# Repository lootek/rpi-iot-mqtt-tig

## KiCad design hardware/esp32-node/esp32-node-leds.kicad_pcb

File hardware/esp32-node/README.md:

# esp32 node v1 - carrier for the 30-pin ESP32 DevKit V1

86 x 54 mm, 2-layer FR-4, DRC clean (KiCad 10: 0 violations, 0 unconnected). Used by the shed, office and dining_room nodes
(see ~/ai/esp32-weather-v2 spec). Populate only what a node needs; the shed needs just the BME280 socket.
Files: `esp32-node.kicad_pcb` + `esp32-node-gerbers.zip` (v1: LEDs external on a 4-way terminal), `esp32-node-leds.kicad_pcb` + `esp32-node-leds-gerbers.zip` (v1b: 3 LEDs soldered on the board), `gen_esp32.py` (regenerates both; `--leds-onboard` for v1b), `esp32-wiring.svg/png` (wiring diagram, `gen-esp32-wiring.py`).
Order one of the two Gerber zips. v1b has 5 mm LEDs (green, yellow, red) at the left edge, 7 mm apart, long leg (anode) toward the resistors.

## DevKit and orientation
30-pin DOIT-style DevKit V1 (USB-C, CH340), two 1x15 headers **25.4 mm apart** (10 pitches).
Plan view: USB end of the DevKit at the bottom edge of the PCB (it overhangs a little).
Left header top to bottom: EN VP VN D34 D35 D32 D33 D25 D26 D27 D14 D12 D13 GND VIN.
Right header top to bottom: D23 D22 TX0 RX0 D21 D19 D18 D5 D17 D16 D4 D2 D15 GND 3V3.

## Nets
| ESP32 pin | Signal | Goes to |
|---|---|---|
| 3V3 | 3V3 | BME280 VCC + CSB, SCD30 VIN, DHT22 +, C1 |
| GND | GND | ground pour on both layers, BME280 GND + SDO, SCD30 GND, DHT22 -, LED cathodes |
| D21 | SDA | BME280 SDA, SCD30 SDA |
| D22 | SCL | BME280 SCL, SCD30 SCL |
| D4 | DHT data | DHT22 DAT |
| D25 / D26 / D27 | LED green / yellow / red | 220 ohm each, then the LED terminal |

BME280 address pins are tied on the board (CSB to 3V3 = I2C mode, SDO to GND = address 0x76).
The DHT22 terminal expects a 3-pin module with its own pull-up; a bare 4-pin DHT22 needs a 10k from DAT to 3V3 added by hand.

## Connectors (5.08 mm screw terminals, wire entry faces the board edge)
- LED terminal, left edge, top to bottom: **G Y R K**. Each LED anode to its terminal, all cathodes to K. 220 ohm resistors R3-R5 are on the board.
- SCD30 terminal, right edge, top to bottom: **3V3 GND SCL SDA**.
- DHT22 terminal, right edge, top to bottom: **3V3 DAT GND**.
- BME280: 1x6 female socket, pins VCC GND SCL SDA CSB SDO (GY-BME280 order). Plug the module so it lies to the **right** of the socket (away from the DevKit).

## BOM
| Ref | Part |
|---|---|
| J1, J2 | 1x15 female header 2.54 mm, 2 pcs (DevKit sockets) |
| J3 | 4-pole screw terminal 5.08 mm (LEDs) |
| J4 | 1x6 female header 2.54 mm (BME280) |
| J5 | 4-pole screw terminal 5.08 mm (SCD30) |
| J6 | 3-pole screw terminal 5.08 mm (DHT22) |
| R3-R5 | 220 ohm 1/4 W axial |
| C1 | 100 nF ceramic disc, 2.5 mm lead spacing |

## Order settings
2 layers, 86 x 54 mm, qty 5+, FR-4 1.6 mm, HASL, no assembly. Upload `esp32-node-gerbers.zip` as is.

## Check before ordering
- Row spacing 25.4 mm was derived from the DevKit photos (11 holes counted inclusively on the perfboard = 10 pitches); measure your DevKit's pin rows once with a ruler.
- Terminal wire-entry side was confirmed from the KiCad 3D model, not a datasheet.
- Not test-fitted on real hardware. The BME280 module must not extend left over the DevKit.

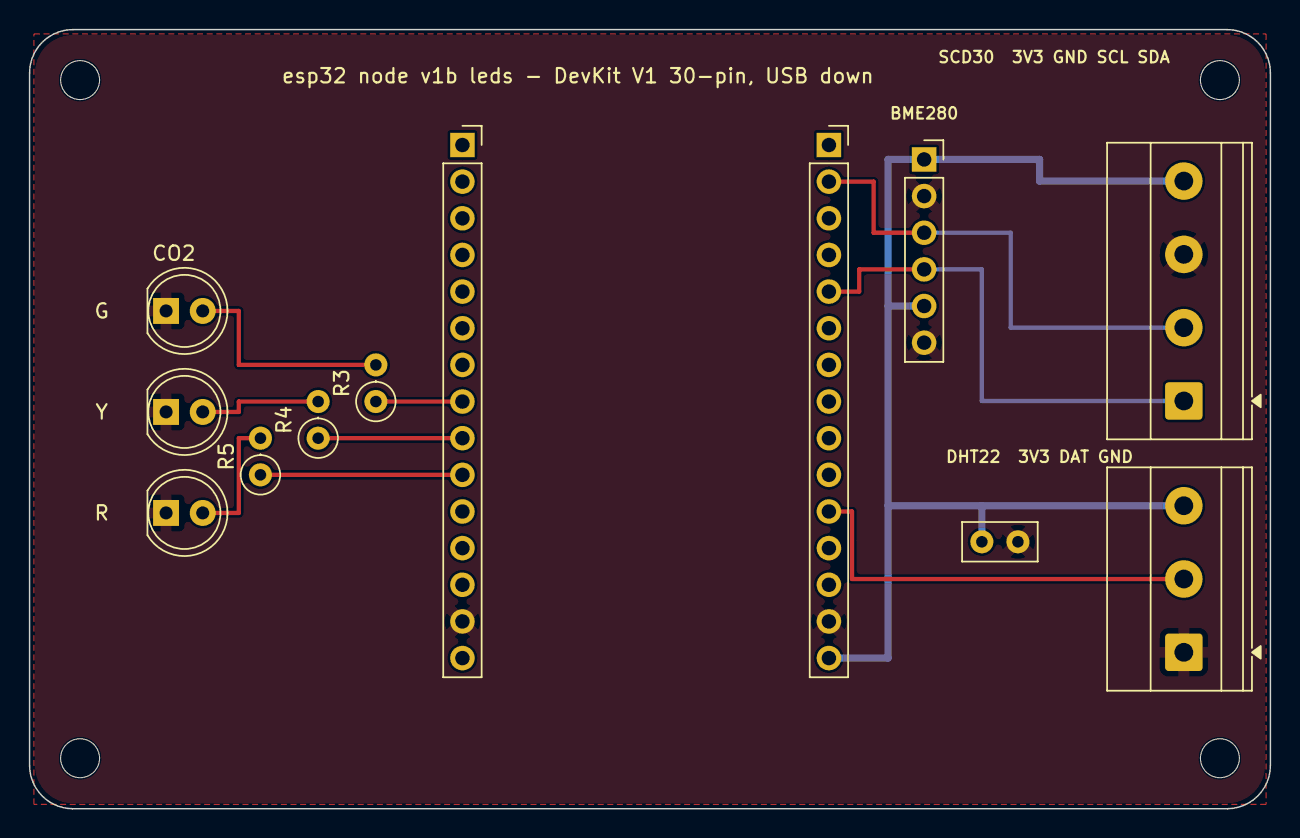
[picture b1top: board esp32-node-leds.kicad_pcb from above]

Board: 2 copper layers, 86.0 x 54.0 mm, 16 parts (0 on the bottom side), 11 nets.

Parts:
C1: 100n; C_Disc_D5.0mm_W2.5mm_P2.50mm
D1, D2, D3: LED; LED_D5.0mm
H1, H2, H3, H4: M2.5; MountingHole_2.7mm_M2.5
J1: ESP32 left; PinSocket_1x15_P2.54mm_Vertical
J2: ESP32 right; PinSocket_1x15_P2.54mm_Vertical
J4: BME280; PinSocket_1x06_P2.54mm_Vertical
J5: SCD30; TerminalBlock_Phoenix_MKDS-1,5-4-5.08_1x04_P5.08mm_Horizont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
J6: DHT22; TerminalBlock_Phoenix_MKDS-1,5-3-5.08_1x03_P5.08mm_Horizont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
R3, R4, R5: 220; R_Axial_DIN0207_L6.3mm_D2.5mm_P2.54mm_Vertical

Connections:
3V3: C1.1, J2.15, J4.1, J4.5, J5.4, J6.3
DHT: J2.11, J6.2
GND: C1.2, D1.1, D2.1, D3.1, J1.14, J2.14, J4.2, J4.6, J5.3, J6.1
G_A: D1.2, R3.2
LED_G: J1.8, R3.1
LED_R: J1.10, R5.1
LED_Y: J1.9, R4.1
R_A: D3.2, R5.2
SCL: J2.2, J4.3, J5.2
SDA: J2.5, J4.4, J5.1
Y_A: D2.2, R4.2

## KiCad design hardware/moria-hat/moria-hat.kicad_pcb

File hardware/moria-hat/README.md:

# moria hat v1 - Pi Zero W sensor hat

65 x 30 mm, 2-layer FR-4, standard Pi Zero pHAT outline (M2.5 holes 58 x 23 mm).
Screw terminals for 2x DS18B20 (1-Wire, GPIO4) and 1x DHT22 (GPIO17), 4.7 k pull-up and a 100 nF cap on board.
DRC clean (KiCad 10, 0 violations, 0 unconnected). Files: `moria-hat.kicad_pcb`, `moria-hat-gerbers.zip` (order this), `gen_hat.py` (regenerates everything).

## Nets
| Pi pin | Signal | Goes to |
|---|---|---|
| 1 | 3V3 | terminal pin 1 (square pad) of J2/J3/J4, R1, C1 |
| 7 | GPIO4 (1-Wire) | terminal pin 2 of J2/J3, R1 other end |
| 11 | GPIO17 | terminal pin 2 of J4 (DHT22) |
| 6, 9, 14, 20, 25, 30, 34, 39 | GND | terminal pin 3, copper pours on both layers |

All three terminals: pin 1 = 3V3 (square pad, left), pin 2 = data, pin 3 = GND (silkscreen: 3V3 / DAT / GND).
DS18B20 probe wires: red = 3V3, yellow (or white) = DAT, black = GND. Wire entry faces the bottom long edge, away from the GPIO header.

## BOM
| Ref | Part |
|---|---|
| J1 | 2x20 female header, 2.54 mm, straight; soldered on the **underside**, plugs onto the Pi's male header |
| J2-J4 | 3-pole screw terminal, 5.08 mm pitch (ARK / KF128-5.08-3P), 3 pcs |
| R1 | 4.7 kOhm, 1/4 W axial |
| C1 | 100 nF ceramic disc, 2.5 mm lead spacing |

The Pi Zero W needs a male 2x20 header soldered to it. Without the socket you can also solder the hat straight onto the Pi's header pins (all 40 holes are plated).

## Order settings (JLCPCB or similar)
2 layers, 65 x 30 mm, qty 5+, FR-4 1.6 mm, HASL (lead-free), any solder mask colour, no assembly.
Upload `moria-hat-gerbers.zip` as is (Gerber + Excellon drill, PTH and NPTH separate).

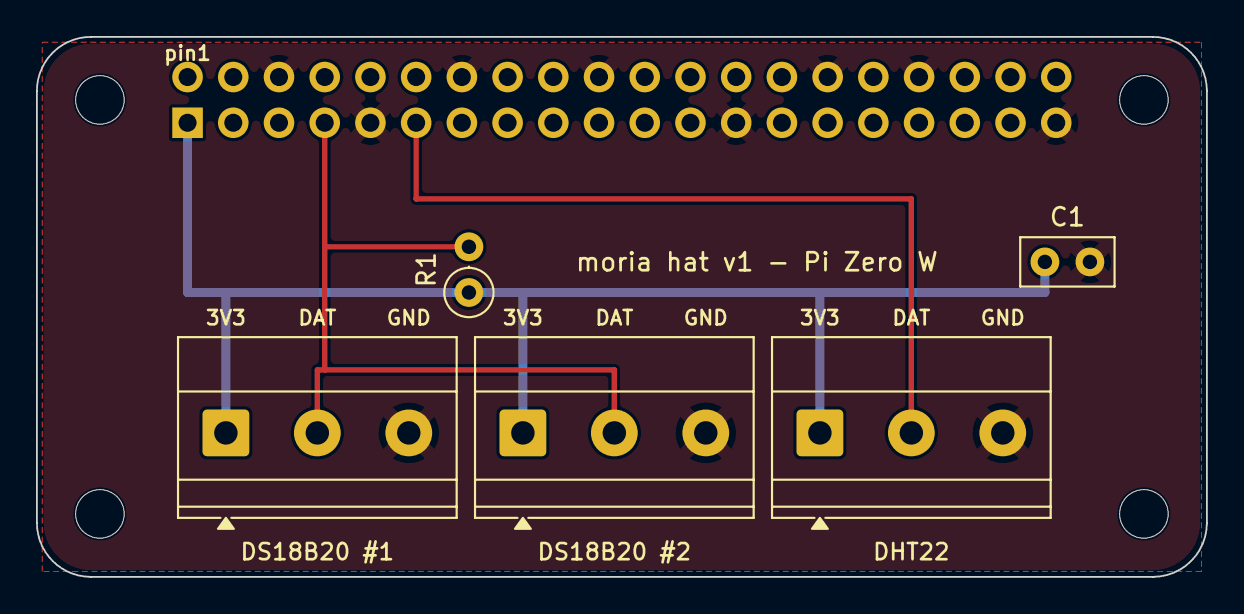
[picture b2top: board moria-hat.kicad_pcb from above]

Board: 2 copper layers, 65.0 x 30.0 mm, 10 parts (1 on the bottom side), 4 nets.

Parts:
C1: 100n; C_Disc_D5.0mm_W2.5mm_P2.50mm
H1, H2, H3, H4: M2.5; MountingHole_2.7mm_M2.5
J1: Pi GPIO; PinSocket_2x20_P2.54mm_Vertical
J2: DS18B20 #1; TerminalBlock_Phoenix_MKDS-1,5-3-5.08_1x03_P5.08mm_Horizont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
J3: DS18B20 #2; TerminalBlock_Phoenix_MKDS-1,5-3-5.08_1x03_P5.08mm_Horizont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
J4: DHT22; TerminalBlock_Phoenix_MKDS-1,5-3-5.08_1x03_P5.08mm_Horizont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
R1: 4.7k; R_Axial_DIN0207_L6.3mm_D2.5mm_P2.54mm_Vertical

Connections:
3V3: C1.1, J1.1, J2.1, J3.1, J4.1, R1.1
DHT: J1.11, J4.2
GND: C1.2, J1.6, J1.9, J1.14, J1.20, J1.25, J1.30, J1.34, J1.39, J2.3, J3.3, J4.3
ONEWIRE: J1.7, J2.2, J3.2, R1.2

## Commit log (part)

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2025-04-13 switch to lothlorien, fix telefraf influx IP
2025-04-13 fix influx IP for telegraf
2025-06-19 Bump urllib3 from 2.1.0 to 2.5.0 in /iot/dht22
    Bumps [urllib3](https://github.com/urllib3/urllib3) from 2.1.0 to 2.5.0.
    - [Release notes](https://github.com/urllib3/urllib3/releases)
    - [Changelog](https://github.com/urllib3/urllib3/blob/main/CHANGES.rst)
    - [Commits](https://github.com/urllib3/urllib3/compare/2.1.0...2.5.0)
    ---
    updated-dependencies:
2025-07-02 cleanup mqtt listener, add overwrite for arbor->shed, switch dht22 to lothlorien
2025-07-10 fix backyard_shed name rewrite
2025-07-10 rewrite ADS1263 + SCT013-030 with Gemini
2025-07-12 reverting AI buggy suggestions
2025-11-28 Fix DNS collector
2025-12-06 Bump urllib3 from 2.1.0 to 2.6.0 in /central-stack
    Bumps [urllib3](https://github.com/urllib3/urllib3) from 2.1.0 to 2.6.0.
    - [Release notes](https://github.com/urllib3/urllib3/releases)
    - [Changelog](https://github.com/urllib3/urllib3/blob/main/CHANGES.rst)
    - [Commits](https://github.com/urllib3/urllib3/compare/2.1.0...2.6.0)
    ---
    updated-dependencies:
2025-12-06 Bump urllib3 from 2.1.0 to 2.6.0 in /iot/dht22
    Bumps [urllib3](https://github.com/urllib3/urllib3) from 2.1.0 to 2.6.0.
    - [Release notes](https://github.com/urllib3/urllib3/releases)
    - [Changelog](https://github.com/urllib3/urllib3/blob/main/CHANGES.rst)
    - [Commits](https://github.com/urllib3/urllib3/compare/2.1.0...2.6.0)
    ---
    updated-dependencies:
2026-01-02 The issue you are experiencing—losing connection and constantly re-authenticating—is likely caused by Client ID conflicts and improper cleanup of the MQTT client.
    In dht22.py, when an exception occurs (e.g., a sensor read error or publish failure), the inner loop breaks, the script waits 5 minutes, and then creates a new MQTT client with the same client_id. Ho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
    Additionally, using client.connect() inside on_disconnect conflicts with the auto
2026-01-02 There are three significant issues with the current implementation regarding the "math" and correctness:
    ADC Conversion Math: The formula (2 - raw_data[i]) for handling negative values from the ADC is incorrect for standard 32-bit signed integers (two's complement). This will result in erroneous current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
    Sampling Strategy (Nyquist Frequency): The current code interleaves sampling of all 10 channels (ADS1263_GetAll) inside the loop. This introduces significant delay between samples for any single chan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
2026-01-02 grafana sending emails pt #1
2026-01-02 fixing docker monitoring
2026-01-02 merge
2026-01-02 grafana ini chmod
2026-01-02 ignore
2026-01-02 dht22 take the hostname dynamically
2026-01-02 The current MQTT connectivity error handling in sct013.py has a few issues that prevent robust self-recovery and could lead to resource exhaustion over time.
    Analysis:
    on_disconnect Callback: The current implementation explicitly calls client.connect() inside the on_disconnect callback. Since you are using client.loop_start(), the Paho MQTT library runs a backgroun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
    Resource Leak (Thread Leak): In the main execution loop, if an exception occurs (e.g., publish fails due to connection loss)
2026-01-03 setting hostname dynamically
2026-01-03 install docker script
2026-01-03 changes around patching
2026-01-03 dht22 dockerfile
2026-01-03 debugging dht22 broken by Gemini
2026-01-03 fixing hostname
2026-01-08 Bump urllib3 from 2.1.0 to 2.6.3 in /central-stack
    Bumps [urllib3](https://github.com/urllib3/urllib3) from 2.1.0 to 2.6.3.
    - [Release notes](https://github.com/urllib3/urllib3/releases)
    - [Changelog](https://github.com/urllib3/urllib3/blob/main/CHANGES.rst)
    - [Commits](https://github.com/urllib3/urllib3/compare/2.1.0...2.6.3)
    ---
    updated-dependencies:
2026-01-22 Bump wheel from 0.41.2 to 0.46.2 in /iot/sct013
    Bumps [wheel](https://github.com/pypa/wheel) from 0.41.2 to 0.46.2.
    - [Release notes](https://github.com/pypa/wheel/releases)
    - [Changelog](https://github.com/pypa/wheel/blob/main/docs/news.rst)
    - [Commits](https://github.com/pypa/wheel/compare/0.41.2...0.46.2)
    ---
    updated-dependencies:
2026-01-22 Bump wheel from 0.41.2 to 0.46.2 in /central-stack
    Bumps [wheel](https://github.com/pypa/wheel) from 0.41.2 to 0.46.2.
    - [Release notes](https://github.com/pypa/wheel/releases)
    - [Changelog](https://github.com/pypa/wheel/blob/main/docs/news.rst)
    - [Commits](https://github.com/pypa/wheel/compare/0.41.2...0.46.2)
    ---
    updated-dependencies:
2026-01-22 Bump wheel from 0.41.2 to 0.46.2 in /iot/dht22
    Bumps [wheel](https://github.com/pypa/wheel) from 0.41.2 to 0.46.2.
    - [Release notes](https://github.com/pypa/wheel/releases)
    - [Changelog](https://github.com/pypa/wheel/blob/main/docs/news.rst)
    - [Commits](https://github.com/pypa/wheel/compare/0.41.2...0.46.2)
    ---
    updated-dependencies:
2026-01-23 [Codex] Updated mqtt-listener.py to keep the process alive: corrected MQTT callback signatures, added reconnect delay support, and wrapped message handling with defensive parsing/logging so unexpecte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
2026-01-25 [Codex] Implemented pushing qir quality measurements to AQICN
2026-02-05 AQICN only for patio
2026-02-05 Bump the pip group across 3 directories with 6 updates
    Bumps the pip group with 6 updates in the /central-stack directory:
    | Package | From | To |
    | --- | --- | --- |
    | [certifi](https://github.com/certifi/python-certifi) | `2023.11.17` | `2024.7.4` |
    | [idna](https://github.com/kjd/idna) | `3.6` | `3.7` |
    | [requests](https://github.com/psf/requests) | `2.31.0` | `2.32.4` |
2026-02-05 working on aqicn
2026-02-06 fixing aqicn
2026-02-06 get env passed
2026-02-06 don't print out token
2026-02-06 aqicn throttling 5 min
2026-03-26 Bump the pip group across 3 directories with 1 update
    Bumps the pip group with 1 update in the /central-stack directory: [requests](https://github.com/psf/requests).
    Bumps the pip group with 1 update in the /iot/dht22 directory: [requests](https://github.com/psf/requests).
    Bumps the pip group with 1 update in the /iot/sct013 directory: [requests](https://github.com/psf/requests).
    Updates `requests` from 2.32.4 to 2.33.0
    - [Release notes](https://github.com/psf/requests/releases)
    - [Changelog](https://github.com/psf/requests/blob/main/HISTORY.md)
2026-05-11 Bump the pip group across 3 directories with 1 update
    Bumps the pip group with 1 update in the /central-stack directory: [urllib3](https://github.com/urllib3/urllib3).
    Bumps the pip group with 1 update in the /iot/dht22 directory: [urllib3](https://github.com/urllib3/urllib3).
    Bumps the pip group with 1 update in the /iot/sct013 directory: [urllib3](https://github.com/urllib3/urllib3).
    Updates `urllib3` from 2.6.3 to 2.7.0
    - [Release notes](https://github.com/urllib3/urllib3/releases)
    - [Changelog](https://github.com/urllib3/urllib3/blob/main/CHANGES.rst)
2026-05-20 Bump the pip group across 3 directories with 1 update
    Bumps the pip group with 1 update in the /central-stack directory: [idna](https://github.com/kjd/idna).
    Bumps the pip group with 1 update in the /iot/dht22 directory: [idna](https://github.com/kjd/idna).
    Bumps the pip group with 1 update in the /iot/sct013 directory: [idna](https://github.com/kjd/idna).
    Updates `idna` from 3.7 to 3.15
    - [Release notes](https://github.com/kjd/idna/releases)
    - [Changelog](https://github.com/kjd/idna/blob/master/HISTORY.md)
2026-06-23 Bump the pip group across 3 directories with 1 update
    Bumps the pip group with 1 update in the /central-stack directory: [msgpack](https://github.com/msgpack/msgpack-python).
    Bumps the pip group with 1 update in the /iot/dht22 directory: [msgpack](https://github.com/msgpack/msgpack-python).
    Bumps the pip group with 1 update in the /iot/sct013 directory: [msgpack](https://github.com/msgpack/msgpack-python).
    Updates `msgpack` from 1.0.7 to 1.2.1
    - [Release notes](https://github.com/msgpack/msgpack-python/releases)
    - [Changelog](https://github.com/msgpack/msgpack-python/blob/main/CHANGELOG.md)
